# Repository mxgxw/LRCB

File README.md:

Nombre de tu proyecto
=====================

Escribe aquí una descripción breve de dos o tres párrafos
en donde expliques: ¿Qué es tu proyecto? ¿Para qué sirve? y ¿Cómo
hacerlo funcionar?

Procura no utilizar técnicismos o lenguaje complicado, recuerda
que las personas que leerán esta descripción puede que no tengan
tu mismo nivel de conocimiento o tu misma área de experiencia.

Explica brévemente el funcionamiento esperado de tu proyecto, no es
necesario que escribas todo en detalle, si el funcionamiento requiere
una explicación más detallada puedes hacer referencia a un sitio web
o a otro archivo de texto dentro de la carpeta "docs".

Es muy útil que indiques el nivel de desarrollo de este proyecto sea
"estable", "beta", "incompleto" o "a-penas-funciona".

También puedes agregar en esta sección los créditos correspondientes
si tu proyecto se deriva de otro, nombres o pseudónimos de las
personas que colaboraron, licencia y fecha de última actualización.

Últimas adiciones
=================

Coloca en esta sección los últimos cambios relevantes o correcciones
que hayas realizado a tu proyecto. Es importante que notifiques sobre
cambios que modifiquen el comportamiento de tu proyecto o las salidas
que este genera.

Ejemplo de cambios en la última versión 0.1alpha:

* Agregados textos de ejemplo
* Agregado números de versión

Correcciones:

* Corregidos errores de ortografía

No es necesario que coloques todo el historial de cambios, en vez de eso
puedes crear un archivo en esta carpeta llamado "changelog.txt" con el histórico
completo (preferiblemente en orden cronológico inverso):

> Puede revisar el historial de cambios completo en el archivo changelog.txt

Costo/Lista de Materiales
=========================

Si la lista de materiales de este proyecto es corta puedes incluírla aquí, en
caso contrario puedes crear un archivo llamado "bom.csv" o un archivo de hoja de
cálculo donde puedes detallar la lista de materiales y costos. Procura utilizar
formatos abiertos en la medida de lo posible, por ejemplo eligiendo ODS sobre
Excel.

Pre-requisitos/Requerimientos
=============================

Dedica esta sección a explicar en detalle ¿Qué se requiere para hacer funcionar
tu proyecto?. Debes colocar los requerimientos o pre-requisitos del software
para hacerlo funcionar y herramientas para construirlo.

Para el hardware puedes especificar herramientas o maquinaria específica que se
necesite para construir el proyecto.

Ejemplo:

Requerimientos de software:

* IDE Arduino.

Herramientas requeridas:

* Pinza cortadora de cable.

Construcción y uso
==================

Si el procedimiento de construcción es sencillo, puedes detallarlo en esta
sección, en caso contrario puedes crear un archivo "build.txt" donde detalles el
procedimiento a seguir.

De igual manera si el procedimiento de utilización del software asociado a tu
proyecto es sencillo puedes explicarlo aquí. En caso de que las instrucciones
sean muy extensas, puedes crear un archivo "usage.txt" y hacer referencia
al mismo en esta sección.

Carpetas
========
La estructura de carpetas es muy importante en un proyecto, te permitirá tener
tus proyectos organizados y permitirá a otros compartir fácilmente cambios o 
mejoras. Esta estructura no está escrita en piedra y puedes modificarla según
se adopte mejor a tus necesidades.

Recuerda que dentro de cada carpeta es muy recomendable que incluyas un archivo
llamado "readme.txt" donde detalles los contenidos de la misma.

En la estruuctura de directorios se recomienda incluir por al menos las
siguientes carpetas:

* *doc*: Utiliza esta carpeta para ingresar toda la documentación que consideres
necesaria para tu proyecto. De preferencia utiliza formatos libres como "ODF"
o simples archivos de texto, si puedes crear una página web en HTML recuerda
renombrar el archivo principal como "index.html" para que pueda ser accedido
fácilmente en caso de que alguien copie esta carpeta en un servidor web.
* *src*: Coloca en esta carpeta todos los archivos de código fuente del software
de control de tu proyecto Open Hardware. Si utilizas un IDE como Eclipse o Arduino
copia dentro de src la carpeta del proyecto.
* *dsn* / *diseño*: En esta carpeta coloca todos los archivos para el diseño de tu
proyecto.
  +  *main*: Coloca en esta carpeta los archivos de diseño original que pueden
incluir, pero no limitarse a: Dibujos 2D, diseños 3D, archivos CAD, bibliotecas
de componentes, dibujos técnicos adicionales.
  +  *aux*: Coloca en esta carpeta los archivos de diseño auxiliares que ayuden
a construir tu proyecto. Los archivos de diseño secundario pueden incluír diseños
2D o 3D en formato de intercambio, dibujos técnicos adicionales, formatos listos
para manufactura, artes gráficos adicionales.
* *extra*: Esta carpeta es libre, aquí puedes colocar otros archivos que se
puedan requerir para hacer funcionar o construir tu proyecto. Un ejemplo de ello
puede ser un driver controlador de un dispositivo específico o vínculos a software
relevante, fotografías o videos.

Excepción de responsabilidades
==============================

Es recomendable que incluyas un texto como el siguiente en tus proyectos:

> El presente proyecto se comparte "tal cual" con el único objetivo de que sea útil.
El/los creadores del presente hardware y su software asociado no pueden garantizar su
correcto funcionamiento bajo ninguna circunstancia. El/Los autor/es de este proyecto
no podrá/n hacerse responsable/s de cualquier pérdida de carácter material, personal o
económico a su persona o terceros derivados de la utilización del mismo. Este proyecto
no deberá ser utilizado bajo ninguna circustancia en sistemas de carácter crítico
o sistemas de los cuales dependan vidas de personas de manera directa o indirecta.

Licenciamiento
==============

Agrega aquí la licencia que utilizas en el código fuente de tu proyecto, adicionalmente
agradeceríamos si colocas la nota de atribución de la plantilla al final.

> La plantilla de este README.md ha sido desarrollada por la comunidad openhardware.sv
con el objetivo de facilitar la documentación de proyectos. Esta plantilla está protegida
bajo la licencia CC BY, puedes modificarla y redistribuirla manteniendo esta nota de
atribución del autor.

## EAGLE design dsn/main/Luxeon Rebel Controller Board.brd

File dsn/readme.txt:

Design files
==================

This folder includes the Eagle schematic and PCB layout design files.

Archivos de diseño principal:

* main\Luxeon Rebel Controller Board.sch : Schematic for Eagle.
* main\Luxeon Rebel Controller Board.brd : PCB.

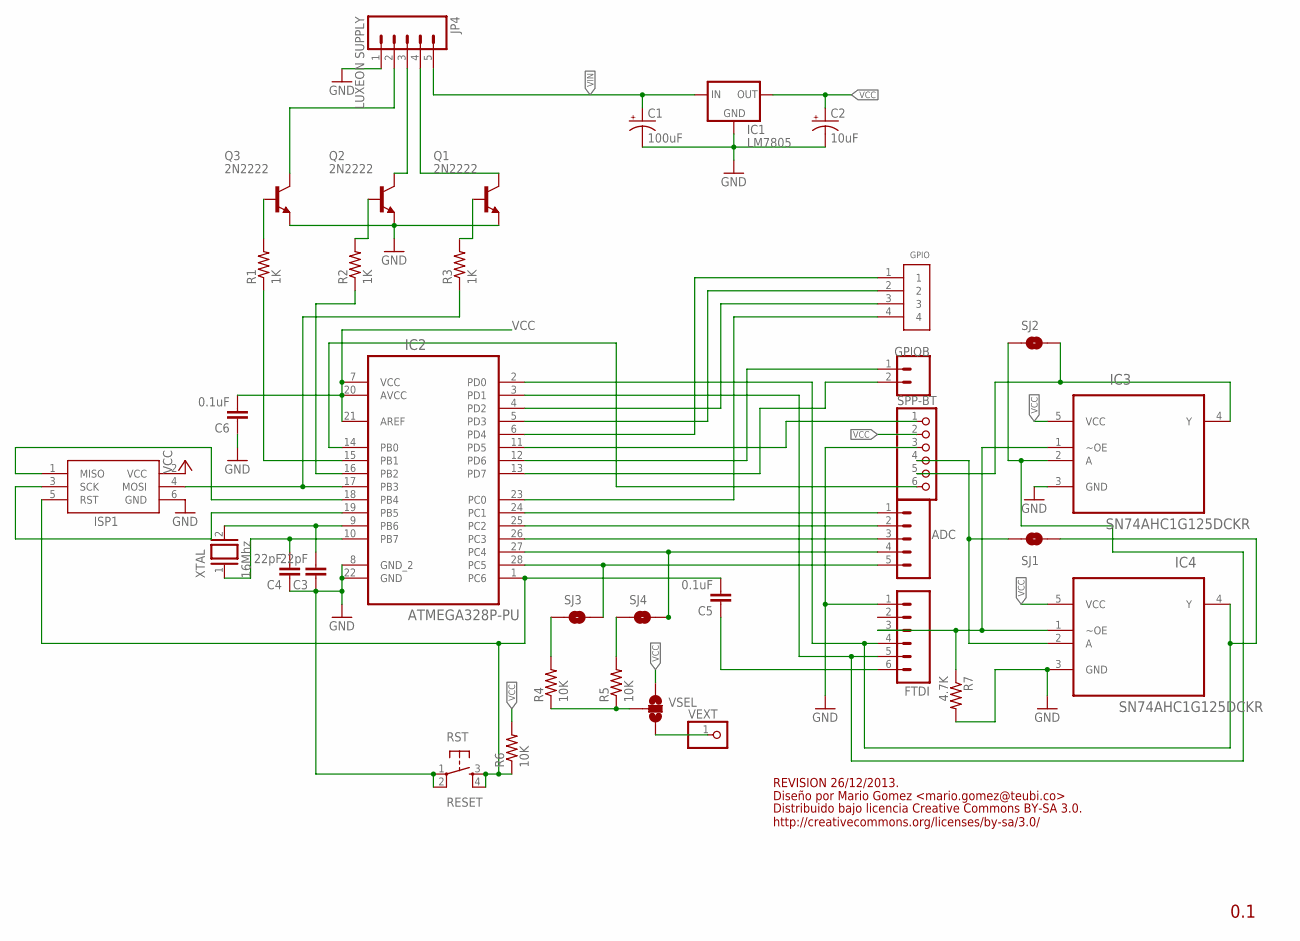
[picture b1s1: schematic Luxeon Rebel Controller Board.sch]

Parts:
ADC: M05PTH; 1X05
C1: 100uF; CPOL-RADIAL-100UF-25V
C2: 10uF; CPOL-RADIAL-10UF-25V
C3, C4: 22pF; CAP-PTH-SMALL
C5, C6: 0.1uF; CAP-PTH-SMALL
FTDI: M06SIP; 1X06
GPIO: 1X4-BIG; 1X04-BIG
GPIOB: M02PTH; 1X02
IC1: LM7805; 78XXL
IC2: ATMEGA328P-PU; DIP254P762X457-28
IC3, IC4: SN74AHC1G125DCKR; SOT65P210X110-5N
ISP1: AVRISP-6; AVRISP
JP4: LUXEON SUPPLY; 1X05_LONGPADS
Q1, Q2, Q3: 2N2222; TO92-EBC-OVAL
R1, R2, R3: 1K; AXIAL-0.3
R4, R5, R6: 10K; AXIAL-0.3
R7: 4.7K; 0603-RES
RST: RESET; TACTILE-PTH
SJ1, SJ2: SOLDERJUMPERNC; SJ_2S
SJ3, SJ4: SOLDERJUMPERTRACE; SJ_2S-TRACE
SPP-BT: PINHD-1X6; 1X06
VEXT: PINHD-1X1; 1X01
VSEL: SOLDERJUMPER_2WAY-OLDS; SJ_3
XTAL: 16Mhz; QS

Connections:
GND: C1.2 (-), C2.2 (-), C3.1, C4.1, C6.1, FTDI.1, IC1.GND, IC2.8 (GND_2), IC2.22 (GND), IC3.3 (GND), IC4.3 (GND), ISP1.6 (GND), JP4.1, Q1.E, Q2.E, Q3.E, R7.2, RST.1, RST.2, SPP-BT.3
unnamed: JP4.2, Q3.C
unnamed: JP4.3, Q2.C
unnamed: JP4.4, Q1.C
unnamed: IC2.15 (PB1), R1.P$1 (1)
unnamed: IC2.16 (PB2), R2.P$1 (1)
unnamed: Q3.B, R1.P$2 (2)
unnamed: Q2.B, R2.P$2 (2)
unnamed: Q1.B, R3.P$2 (2)
unnamed: IC2.17 (PB3), ISP1.4 (MOSI), R3.P$1 (1)
unnamed: C3.2, IC2.9 (PB6), XTAL.2
unnamed: IC2.18 (PB4), ISP1.1 (MISO)
unnamed: ADC.5, IC2.28 (PC5), SJ3.2
unnamed: ADC.4, IC2.27 (PC4), SJ4.2
unnamed: IC4.2 (A), SJ1.1, SPP-BT.4
unnamed: C5.1, FTDI.6
unnamed: FTDI.4, IC2.2 (PD0), IC4.4 (Y), SJ1.2
unnamed: FTDI.3, IC3.1 (~OE), IC4.1 (~OE), R7.1
unnamed: IC2.19 (PB5), ISP1.3 (SCK)
unnamed: C4.2, IC2.10 (PB7), XTAL.1
unnamed: R4.P$2 (2), SJ3.1
unnamed: C5.2, IC2.1 (PC6), ISP1.5 (RST), R6.P$1 (1), RST.3, RST.4
unnamed: IC2.11 (PD5), SPP-BT.1
unnamed: IC2.14 (PB0), SPP-BT.6
unnamed: IC3.4 (Y), SJ2.2, SPP-BT.5
unnamed: R5.P$2 (2), SJ4.1
unnamed: GPIOB.2, IC2.13 (PD7)
unnamed: GPIOB.1, IC2.12 (PD6)
unnamed: ADC.3, IC2.26 (PC3)
unnamed: ADC.2, IC2.25 (PC2)
unnamed: ADC.1, IC2.24 (PC1)
unnamed: R4.P$1 (1), R5.P$1 (1), VSEL.2
unnamed: VEXT.1, VSEL.3
N_PC0: GPIO.4, IC2.23 (PC0)
N_PD1: FTDI.5, IC2.3 (PD1), IC3.2 (A), SJ2.1
N_PD2: GPIO.3, IC2.4 (PD2)
N_PD3: GPIO.2, IC2.5 (PD3)
N_PD4: GPIO.1, IC2.6 (PD4)
VCC: C2.1 (+), C6.2, IC1.OUT, IC2.7 (VCC), IC2.20 (AVCC), IC2.21 (AREF), IC3.5 (VCC), IC4.5 (VCC), ISP1.2 (VCC), R6.P$2 (2), SPP-BT.2, VSEL.1
VIN: C1.1 (+), IC1.IN, JP4.5

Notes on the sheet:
0.1
REVISION 26/12/2013.
Diseño por Mario Gomez <mario.gomez@teubi.co>
Distribuido bajo licencia Creative Commons BY-SA 3.0. http://creativecommons.org/licenses/by-sa/3.0/

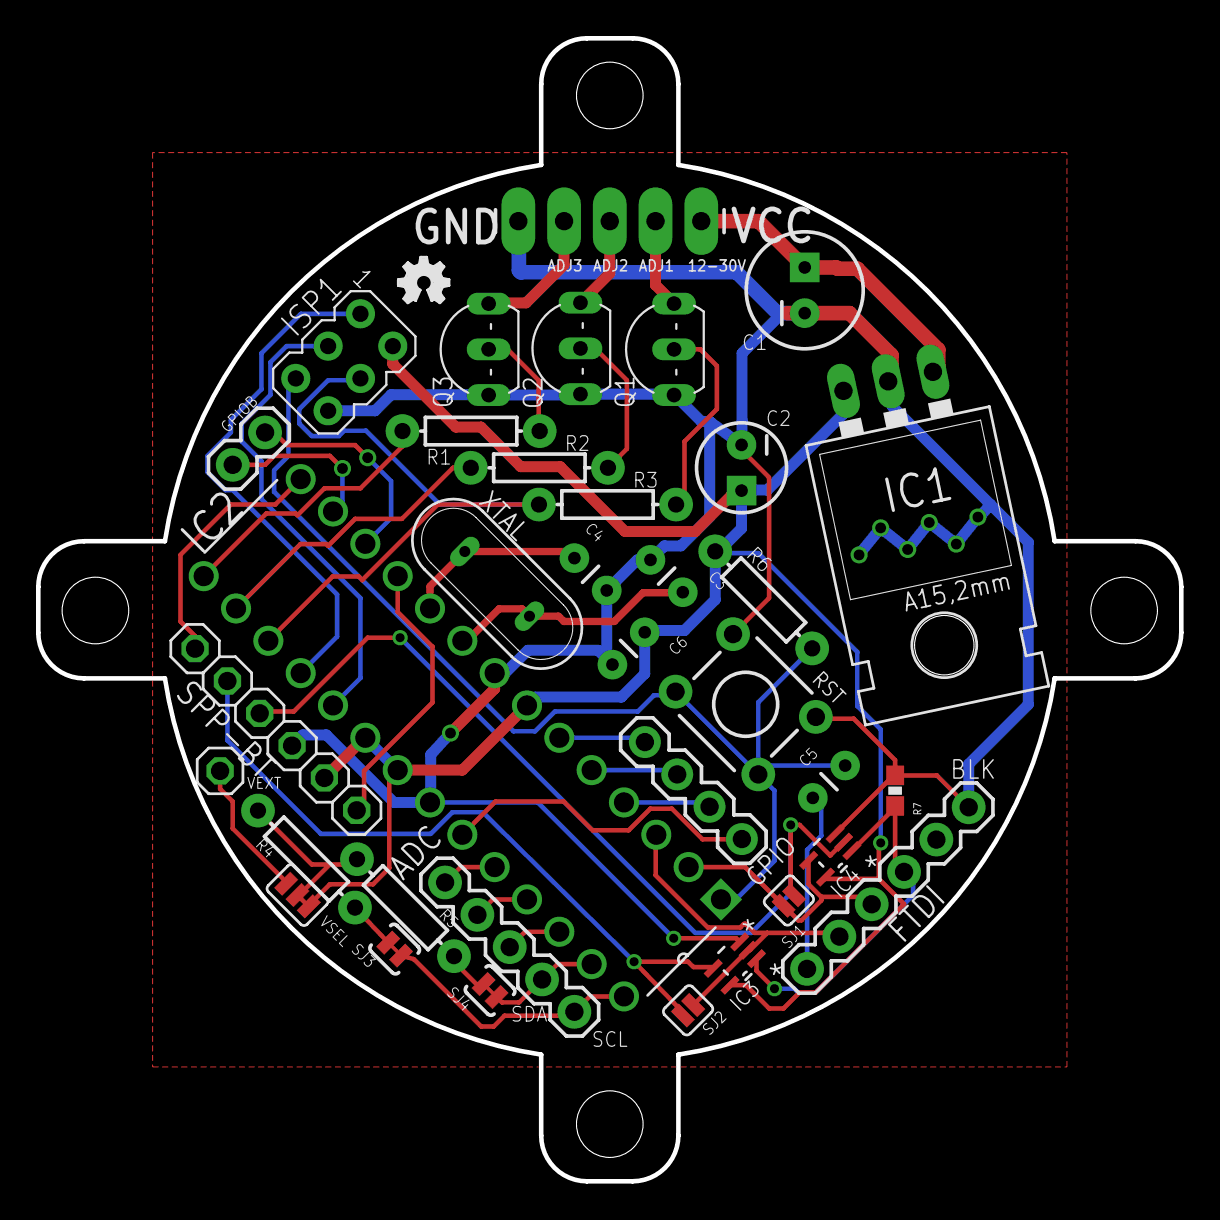
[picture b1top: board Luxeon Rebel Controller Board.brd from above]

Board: 2 copper layers, 63.5 x 63.5 mm, 37 parts (1 on the bottom side), 40 nets.

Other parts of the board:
U$1: LOGOVECTOR2
U$2: OSHW_FILLX100_NOTEXT

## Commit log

2014-01-28 Addded last revision
2014-01-30 fixed names

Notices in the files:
parts and their libraries:
SparkFun-PowerIC: Licensing: CC v3.0 Share-Alike You are welcome to use this library for commercial purposes.
